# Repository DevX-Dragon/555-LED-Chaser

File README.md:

Welcome to my repo.
This is a simple 555 LED CHASER I made for Hack Club Blueprint.

# PCB LAYOUT

# Schematics 

# 3D Renders

# Required Components

 x1 [ne555p](https://www.amazon.com/Juried-Engineering-NE555P-Precision-Breadboard-Friendly/dp/B08D3GH7X3)
 
x10 [LEDS](https://www.amazon.com/dp/B0DRSH4G3K/ref=sspa_dk_detail_1?pd_rd_i=B0DRSH4G3K&pd_rd_w=LLRCU&content-id=amzn1.sym.7446a9d1-25fe-4460-b135-a60336bad2c9&pf_rd_p=7446a9d1-25fe-4460-b135-a60336bad2c9&pf_rd_r=62ZCN9VXXSGJ6R7GSP82&pd_rd_wg=nzuaS&pd_rd_r=d8e3331b-95b5-44ee-9956-1c784ce575d0&sp_csd=d2lkZ2V0TmFtZT1zcF9kZXRhaWw&th=1)

x1 [CD4017](https://www.amazon.com/Bridgold-Decimal-Counter-decoded-Distributor/dp/B08FRJJ98M/ref=sr_1_1_sspa?dib=eyJ2IjoiMSJ9.hpne20G2aAX_6csJuT1G049TJAjZENS56ogpE2CVllSC3bXWqk0-qLnzznclPBHsr1lsHk7AgtH_RJ8DEz0rf2MKNGw0cHapiUZ3A72dXYQXfp24w4XH2BJbR0zl2sOVDLz5hTw1Kg5gHzwYsyrnXGN7mMRRJpaccwg_yEZQ9v5e0zVIUVzNZkD4nAqw2uwexhhalxXxWHm_3QO2eMUQV9mBYN0cM5ZWvwHo1b12ko0.SrqXBrqwByQKagW-0TcnmLWRWfKbBHQXFBTo9Z2prWM&dib_tag=se&keywords=cd4017&qid=1766824736&sr=8-1-spons&sp_csd=d2lkZ2V0TmFtZT1zcF9hdGY&psc=1)

x1 [470 ohms ressistor](https://www.amazon.com/470-ohm-resistor/s?k=470+ohm+resistor)

x1 [1k ohms ressistor](https://www.amazon.com/s?k=1k+ohm+resistor&crid=VX4VIC4YO15Q&sprefix=1k+o%2Caps%2C371&ref=nb_sb_ss_p13n-expert-pd-ops-ranker_1_4)

x1 [50k Potentiometer ](https://www.amazon.com/50k-potentiometer/s?k=50k+potentiometer)

x1 [1 uF polarized capcitor](https://www.amazon.com/1uF-Capacitor/s?k=1uF+Capacitor)

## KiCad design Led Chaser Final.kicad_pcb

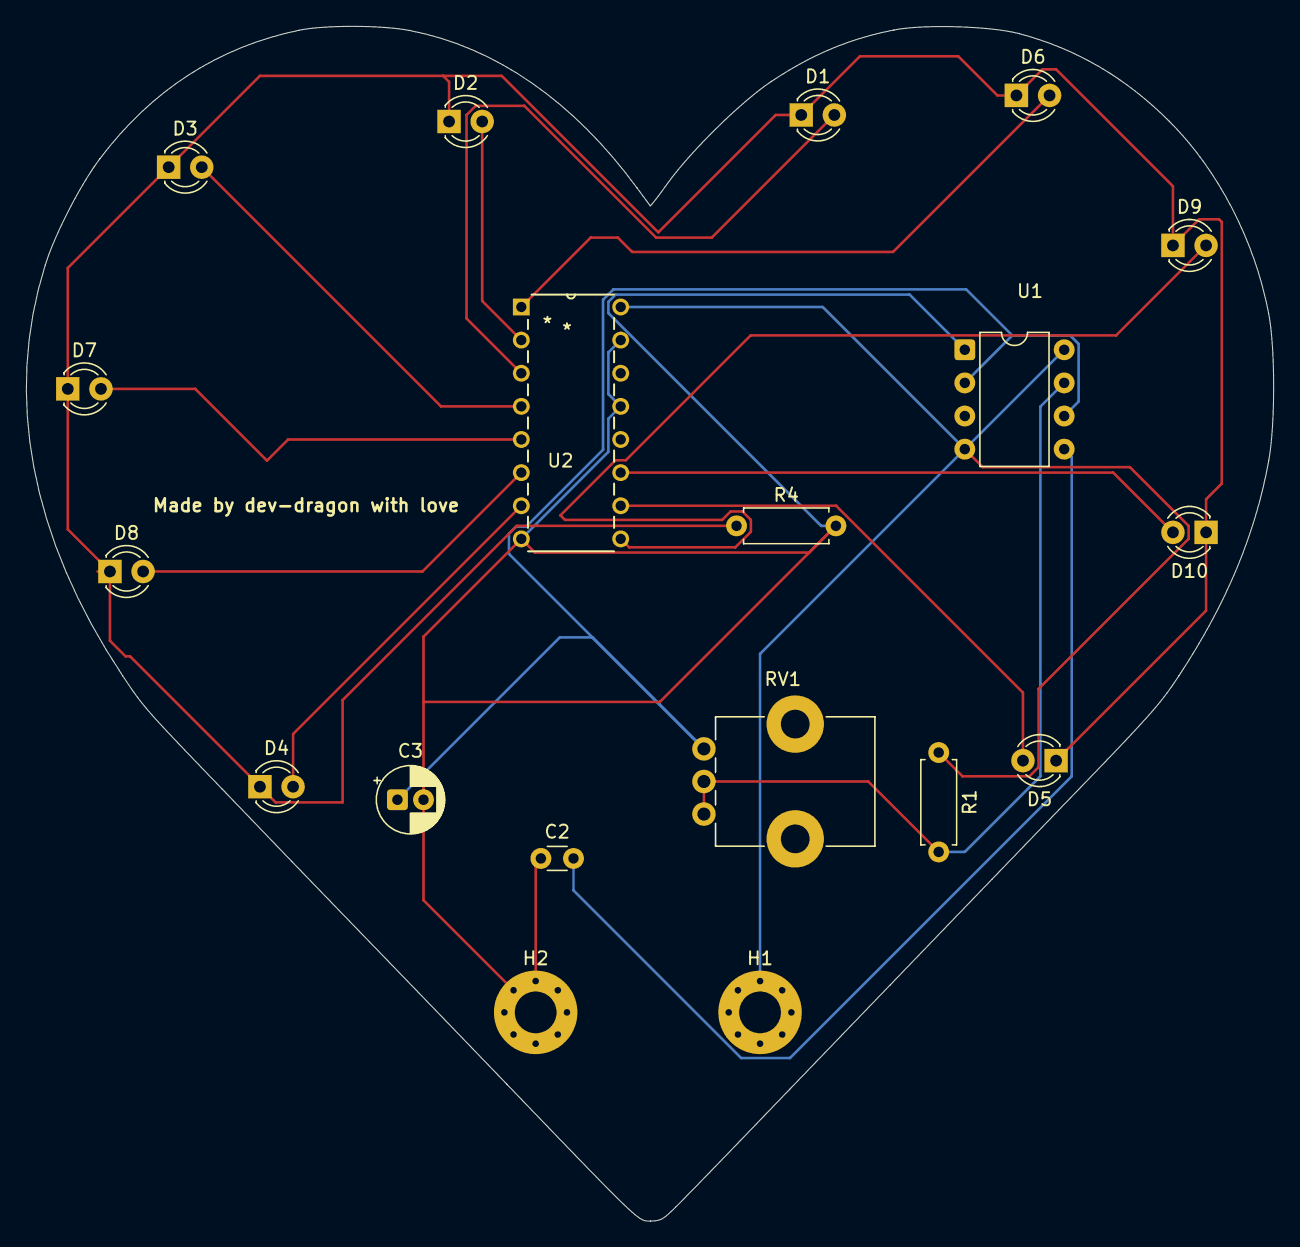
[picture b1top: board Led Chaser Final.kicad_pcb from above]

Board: 2 copper layers, 95.6 x 91.6 mm, 19 parts (0 on the bottom side), 16 nets.

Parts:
C2: C; C_Disc_D3.0mm_W1.6mm_P2.50mm
C3: 1 uF; CP_Radial_D5.0mm_P2.00mm
D1, D2, D3, D4, D5, D6, D7, D8, D9, D10: LED; LED_D3.0mm
H1, H2: MountingHole_Pad; MountingHole_3.2mm_M3_Pad_Via
R1: 1k; R_Axial_DIN0207_L6.3mm_D2.5mm_P7.62mm_Horizontal
R4: 470; R_Axial_DIN0207_L6.3mm_D2.5mm_P7.62mm_Horizontal
RV1: 50k; Potentiometer_Bourns_PTV09A-1_Single_Vertical
U1: NE555P; DIP-8_W7.62mm
U2: 4017; N16

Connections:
+5V: H1.1, R1.1, U1.4 (R), U1.8 (VCC), U2.16 (VDD)
GND: C2.1, C3.2, H2.1, R4.2, U1.1 (GND), U2.8 (VSS), U2.13 (CKEN), U2.15 (Reset)
unnamed: D1.2 (A), U2.3 (Q0)
unnamed: D1.1 (K), D2.1 (K), D3.1 (K), D4.1 (K), D5.1 (K), D6.1 (K), D7.1 (K), D8.1 (K), D9.1 (K), D10.1 (K), R4.1
unnamed: D2.2 (A), U2.2 (Q1)
unnamed: D3.2 (A), U2.4 (Q2)
unnamed: D4.2 (A), U2.7 (Q3)
unnamed: D5.2 (A), U2.10 (Q4)
unnamed: D6.2 (A), U2.1 (Q5)
unnamed: D7.2 (A), U2.5 (Q6)
unnamed: D8.2 (A), U2.6 (Q7)
unnamed: D9.2 (A), U2.9 (Q8)
unnamed: D10.2 (A), U2.11 (Q9)
unnamed: C2.2, U1.5 (CV)
unnamed: R1.2, RV1.1, RV1.2, U1.7 (DIS)
unnamed: C3.1, RV1.3, U1.2 (TR), U1.6 (THR)

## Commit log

2025-12-27 Create Gerber
2025-12-27 Create Layout Images
2025-12-27 Create png
2025-12-27 Create Lol
2025-12-27 Create Hmm
